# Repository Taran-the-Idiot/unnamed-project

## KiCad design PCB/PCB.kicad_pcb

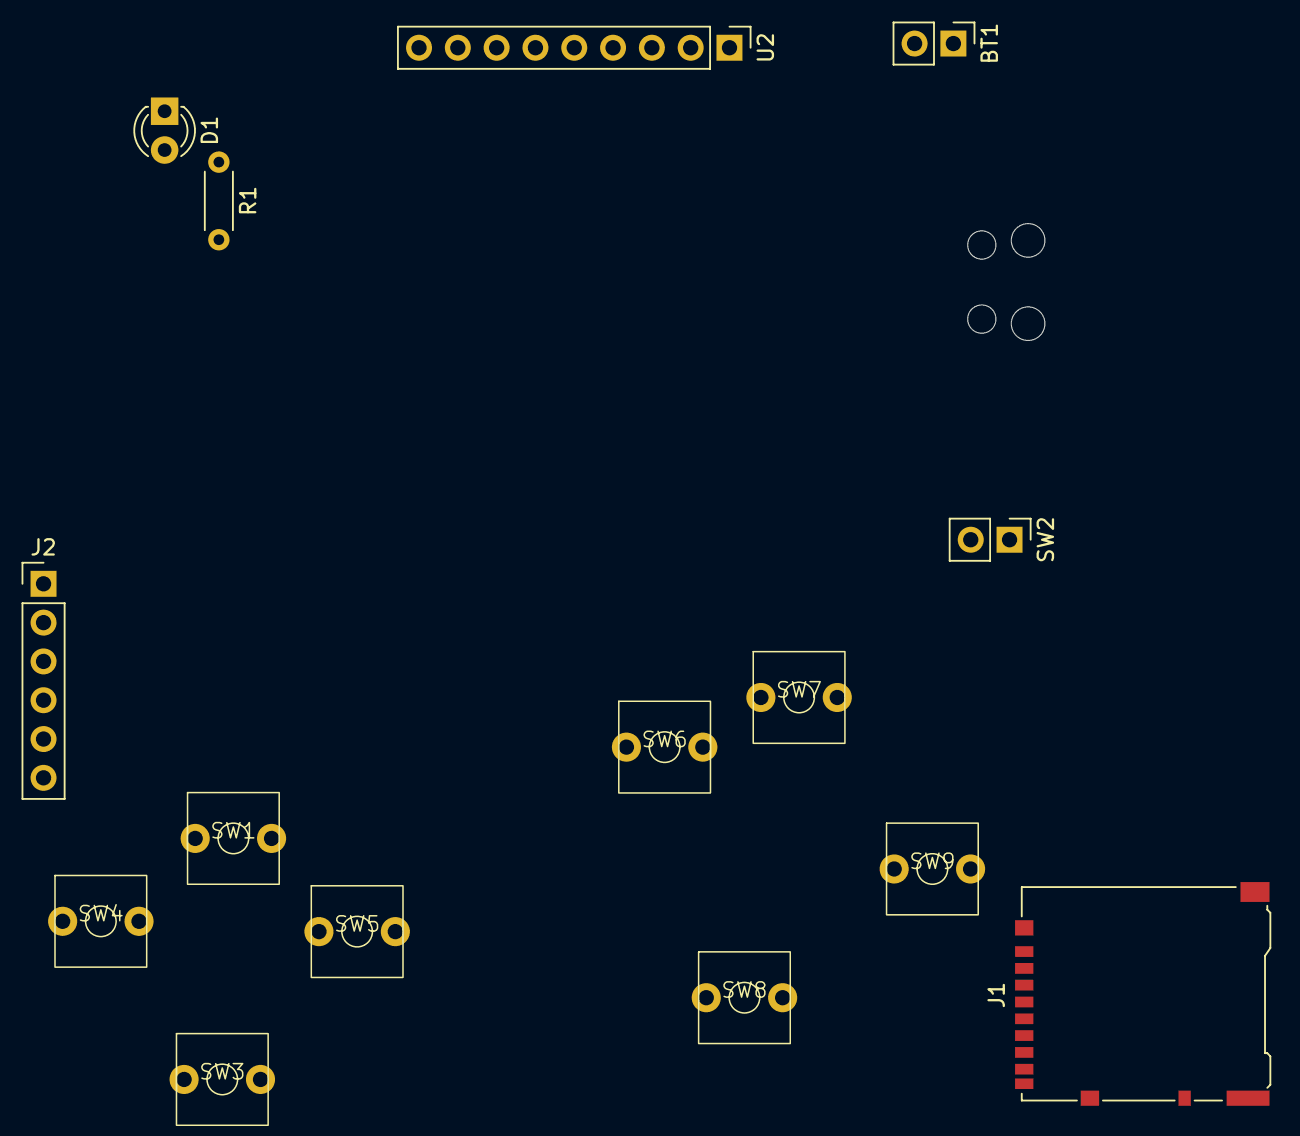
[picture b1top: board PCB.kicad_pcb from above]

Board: 2 copper layers, 16 parts (1 on the bottom side), 6 nets, no tracks yet.

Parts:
BT1: Battery; PinHeader_1x02_P2.54mm_Vertical
D1: LED; LED_D3.0mm
J1: Micro_SD_Card; microSD_HC_Hirose_DM3AT-SF-PEJM5
J2: MAX98357A; PinHeader_1x06_P2.54mm_Vertical
R1: R_Small; R_Axial_DIN0204_L3.6mm_D1.6mm_P5.08mm_Horizontal
SW1, SW3, SW4, SW5, SW6, SW7, SW8, SW9: SW_Push; Button-6mm-2pin-tht
SW2: SW_Slide_DPDT; PinHeader_1x02_P2.54mm_Vertical
U1: Pico; RaspberryPi_Pico_Common_SMD
U2: CR2013-MI2120; PinHeader_1x09_P2.54mm_Vertical

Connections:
+3V3: J1.4 (VDD), U1.36 (3V3), U2.1 (VCC)
+BATT: BT1.1 (+), SW2.2 (B)
GND: BT1.2 (-), D1.1 (K), J1.6 (VSS), J1.9 (SHIELD), J2.6, SW1.2, SW3.2, SW4.2, SW5.2, SW6.2, SW7.2, SW8.2, SW9.2, U1.3 (GND), U1.8 (GND), U1.13 (GND), U1.18 (GND), U1.23 (GND), U1.28 (GND), U1.33 (AGND), U1.38 (GND), U2.2 (GND)
unnamed: D1.2 (A), R1.1
VBUS: R1.2, U1.40 (VBUS)
VS: SW2.1 (A), U1.39 (VSYS)

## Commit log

2026-05-25 potato
2026-05-25 its a gam console. idk thought it would be cool to make one
2026-05-26 the firmware is scaring me. im gonna go back to drivng macropad
2026-05-31 ingore
